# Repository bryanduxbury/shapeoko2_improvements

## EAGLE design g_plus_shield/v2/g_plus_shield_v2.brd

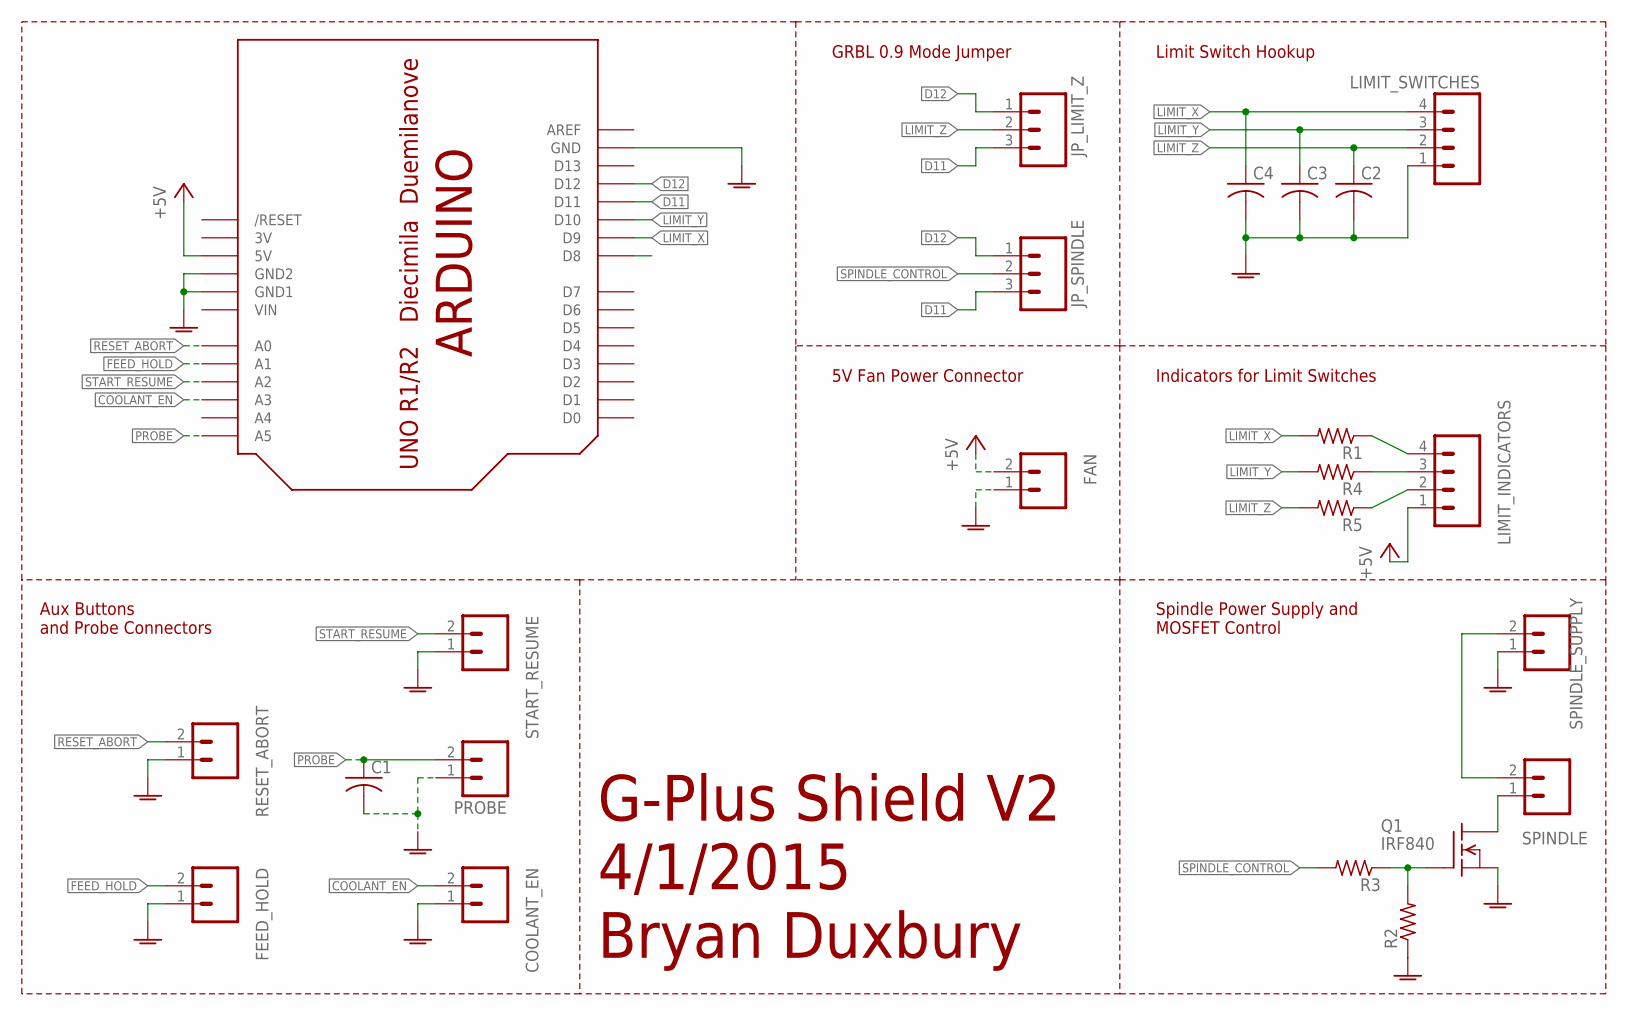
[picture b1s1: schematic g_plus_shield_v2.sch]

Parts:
C1, C2, C3, C4: C-US050-024X044; C050-024X044
COOLANT_EN: M02POLAR; MOLEX-1X2
FAN: M02POLAR; MOLEX-1X2
FEED_HOLD: M02POLAR; MOLEX-1X2
JP_LIMIT_Z: M03POLAR; MOLEX-1X3
JP_SPINDLE: M03POLAR; MOLEX-1X3
LIMIT_INDICATORS: M04POLAR; MOLEX-1X4
LIMIT_SWITCHES: M04POLAR; MOLEX-1X4
PROBE: M02POLAR; MOLEX-1X2
Q1: IRF840; TO220
R1, R2, R3, R4, R5: R-US_0207/7; 0207/7
RESET_ABORT: M02POLAR; MOLEX-1X2
SPINDLE: M02POLAR; MOLEX-1X2
SPINDLE_SUPPLY: M02POLAR; MOLEX-1X2
START_RESUME: M02POLAR; MOLEX-1X2
U$1: ARDUINO-NODIM

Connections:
3V: U$1.3V
48V: SPINDLE.2, SPINDLE_SUPPLY.2
+5V: FAN.2, LIMIT_INDICATORS.1, U$1.5V
COOLANT_EN: COOLANT_EN.2, U$1.A3
D11: JP_LIMIT_Z.3, JP_SPINDLE.3, U$1.D11
D12: JP_LIMIT_Z.1, JP_SPINDLE.1, U$1.D12
FEED_HOLD: FEED_HOLD.2, U$1.A1
GNDA: C1.2, C2.2, C3.2, C4.2, COOLANT_EN.1, FAN.1, FEED_HOLD.1, LIMIT_SWITCHES.1, PROBE.1, Q1.3 (S), R2.1, RESET_ABORT.1, SPINDLE_SUPPLY.1, START_RESUME.1, U$1.GND, U$1.GND1, U$1.GND2
LIMIT_X: C4.1, LIMIT_SWITCHES.4, R1.2, U$1.D9
LIMIT_Y: C3.1, LIMIT_SWITCHES.3, R4.2, U$1.D10
LIMIT_Z: C2.1, JP_LIMIT_Z.2, LIMIT_SWITCHES.2, R5.2
unnamed: LIMIT_INDICATORS.4, R1.1
unnamed: Q1.2 (D), SPINDLE.1
unnamed: Q1.1 (G), R2.2, R3.1
unnamed: LIMIT_INDICATORS.2, R5.1
unnamed: LIMIT_INDICATORS.3, R4.1
PROBE: C1.1, PROBE.2, U$1.A5
RESET_ABORT: RESET_ABORT.2, U$1.A0
SPINDLE_CONTROL: JP_SPINDLE.2, R3.2
START_RESUME: START_RESUME.2, U$1.A2
VIN: U$1.VIN

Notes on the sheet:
GRBL 0.9 Mode Jumper
Limit Switch Hookup
Indicators for Limit Switches
Spindle Power Supply and MOSFET Control
Aux Buttons and Probe Connectors
5V Fan Power Connector
G-Plus Shield V2 4/1/2015 Bryan Duxbury

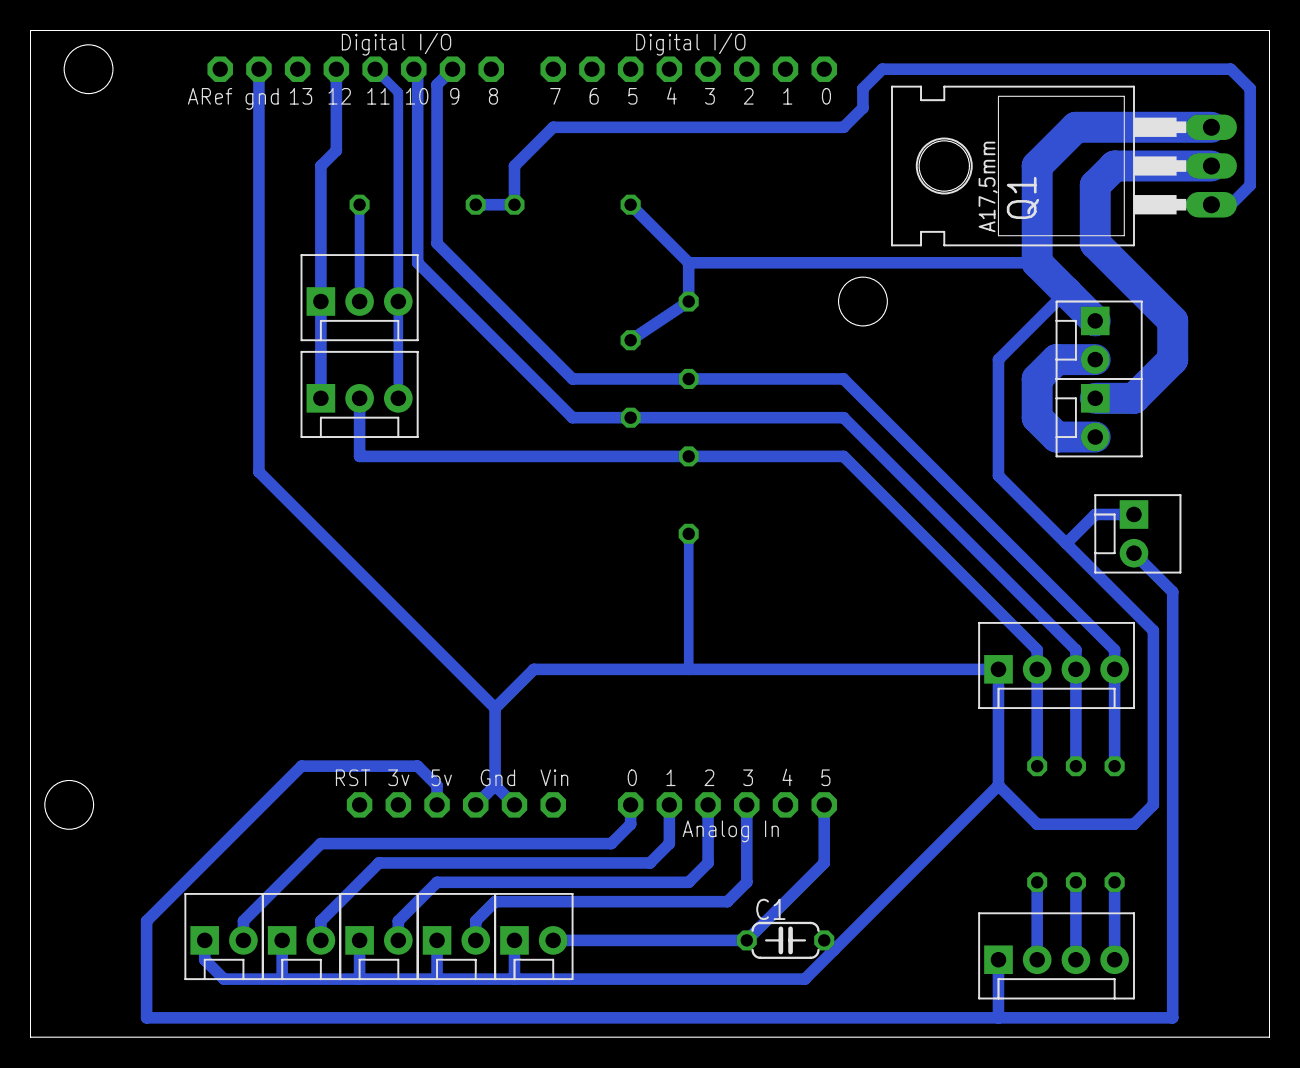
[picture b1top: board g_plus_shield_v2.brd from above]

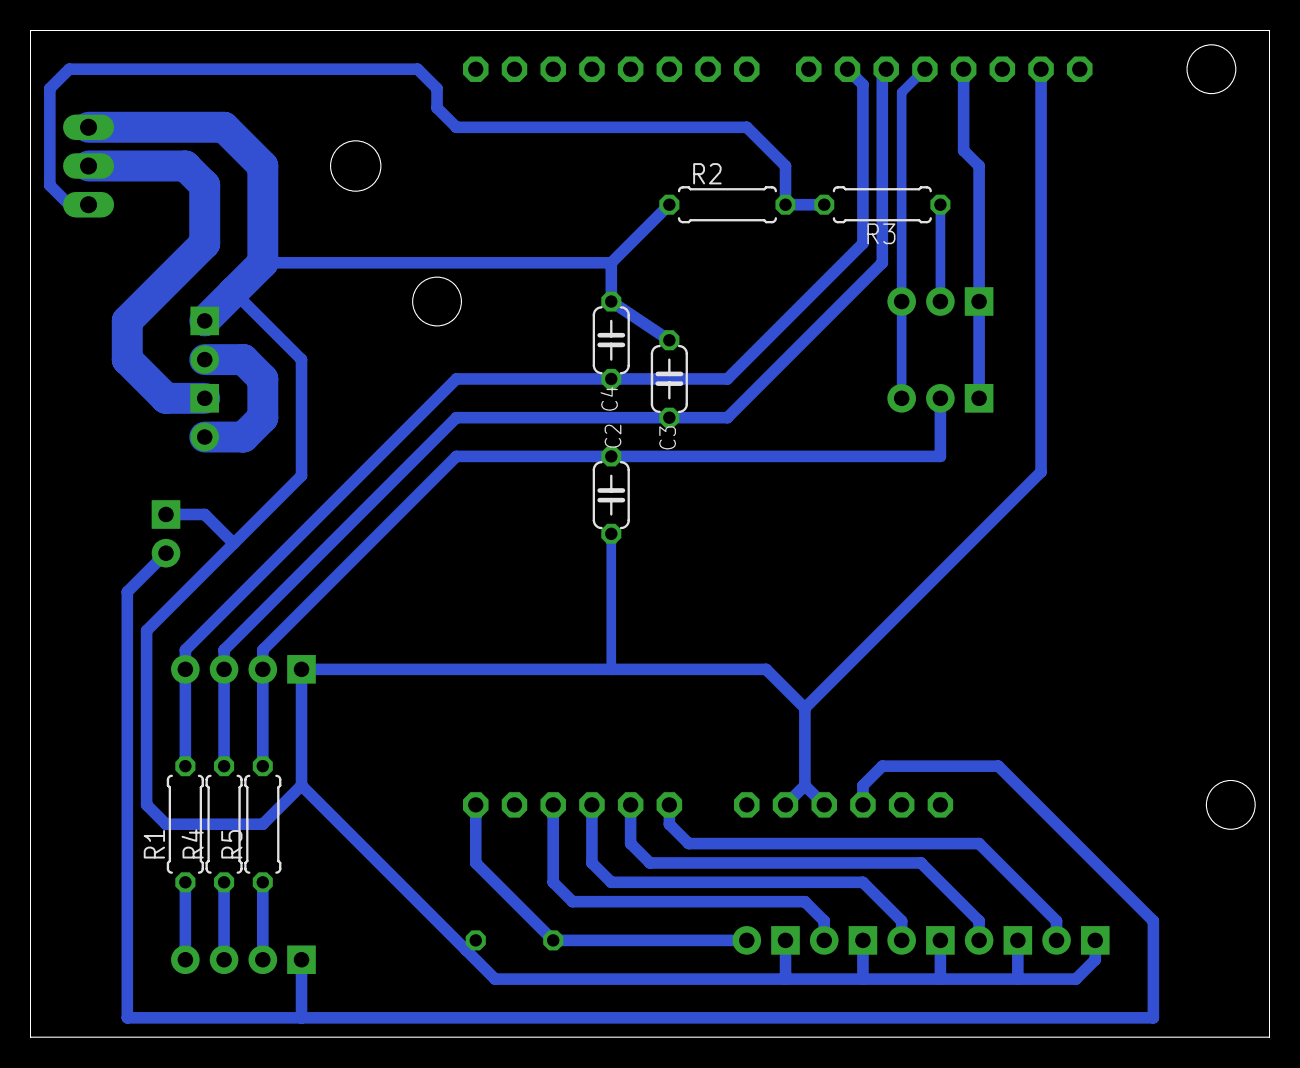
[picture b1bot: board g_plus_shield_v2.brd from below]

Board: 2 copper layers, 81.3 x 66.0 mm, 23 parts (8 on the bottom side), 19 nets.

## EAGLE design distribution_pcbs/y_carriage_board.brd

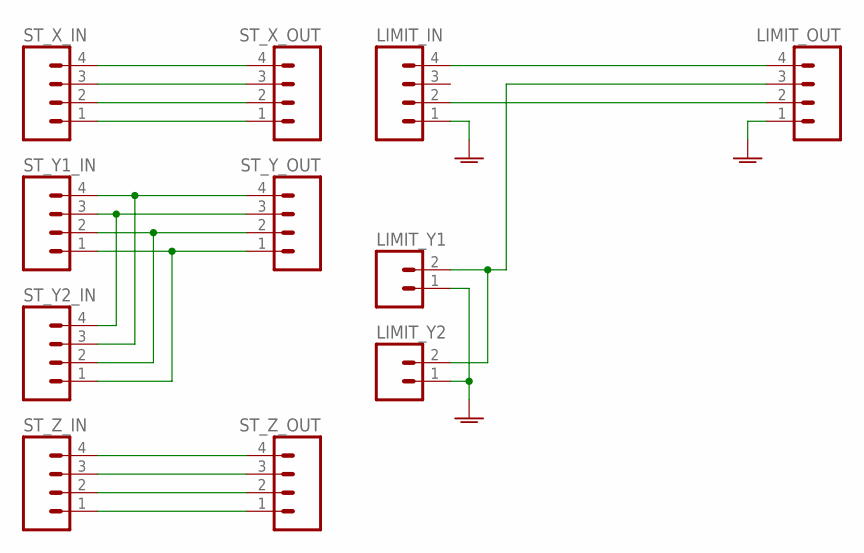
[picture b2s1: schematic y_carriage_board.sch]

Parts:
LIMIT_IN: M04POLAR; MOLEX-1X4
LIMIT_OUT: M04POLAR; MOLEX-1X4
LIMIT_Y1, LIMIT_Y2: M02POLAR; MOLEX-1X2
ST_X_IN: M04POLAR; MOLEX-1X4
ST_X_OUT: M04POLAR; MOLEX-1X4
ST_Y1_IN, ST_Y2_IN: M04POLAR; MOLEX-1X4
ST_Y_OUT: M04POLAR; MOLEX-1X4
ST_Z_IN: M04POLAR; MOLEX-1X4
ST_Z_OUT: M04POLAR; MOLEX-1X4

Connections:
GNDA: LIMIT_IN.1, LIMIT_OUT.1, LIMIT_Y1.1, LIMIT_Y2.1
unnamed: ST_X_IN.4, ST_X_OUT.4
unnamed: ST_X_IN.3, ST_X_OUT.3
unnamed: ST_X_IN.2, ST_X_OUT.2
unnamed: ST_X_IN.1, ST_X_OUT.1
unnamed: ST_Y1_IN.2, ST_Y2_IN.2, ST_Y_OUT.2
unnamed: ST_Y1_IN.1, ST_Y2_IN.1, ST_Y_OUT.1
unnamed: LIMIT_IN.4, LIMIT_OUT.4
unnamed: LIMIT_OUT.3, LIMIT_Y1.2, LIMIT_Y2.2
unnamed: ST_Z_IN.4, ST_Z_OUT.4
unnamed: ST_Z_IN.3, ST_Z_OUT.3
unnamed: ST_Z_IN.2, ST_Z_OUT.2
unnamed: ST_Z_IN.1, ST_Z_OUT.1
unnamed: LIMIT_IN.2, LIMIT_OUT.2
unnamed: ST_Y1_IN.3, ST_Y2_IN.4, ST_Y_OUT.3
unnamed: ST_Y1_IN.4, ST_Y2_IN.3, ST_Y_OUT.4

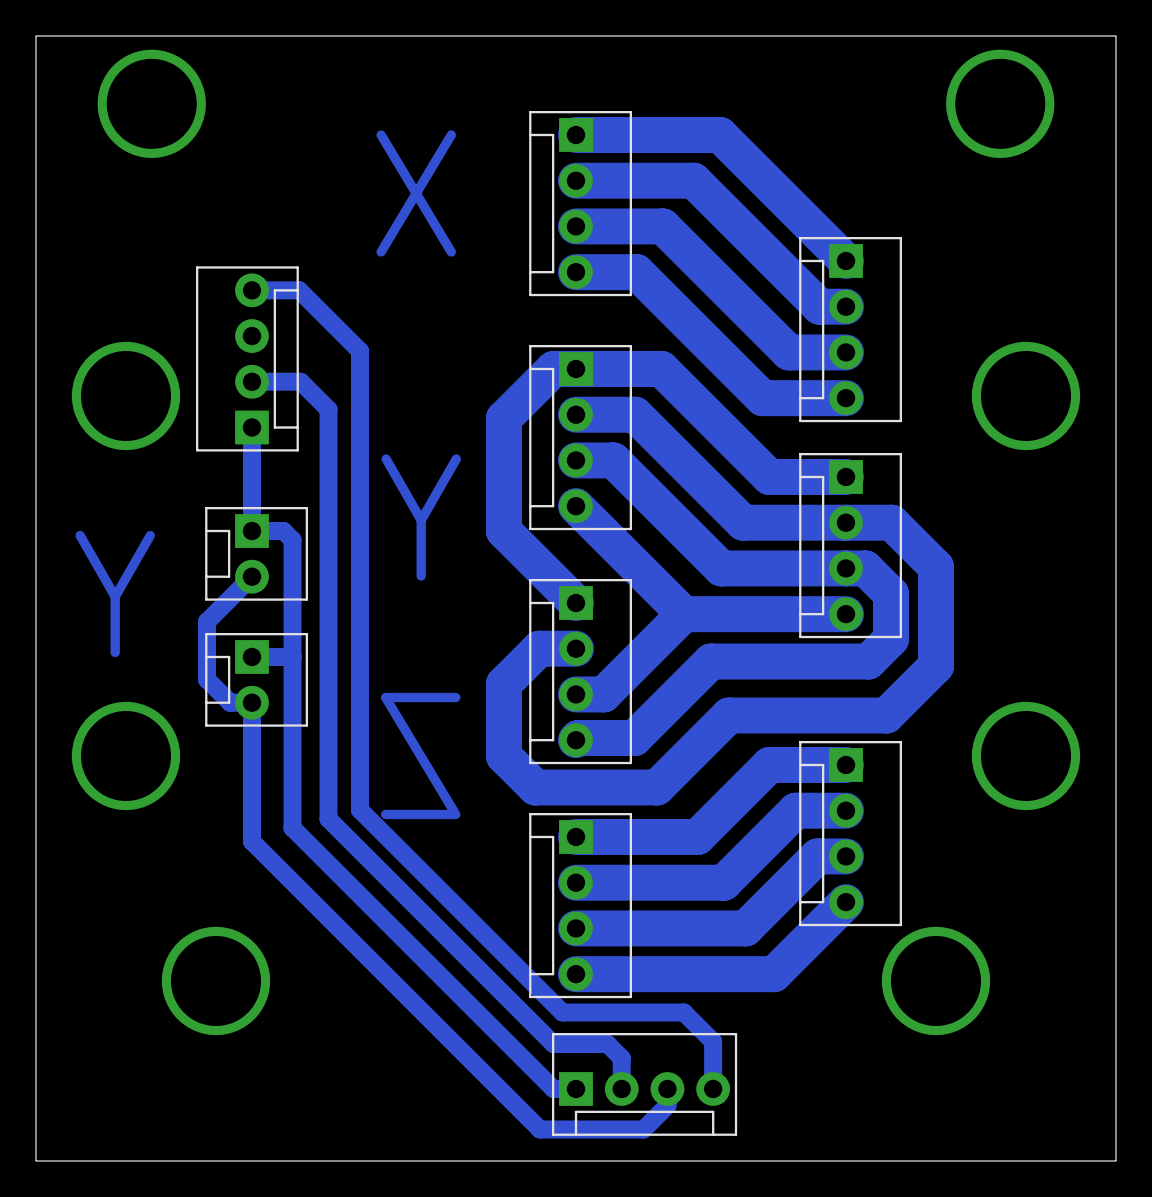
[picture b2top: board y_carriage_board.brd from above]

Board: 2 copper layers, 60.0 x 62.5 mm, 11 parts (0 on the bottom side), 16 nets.

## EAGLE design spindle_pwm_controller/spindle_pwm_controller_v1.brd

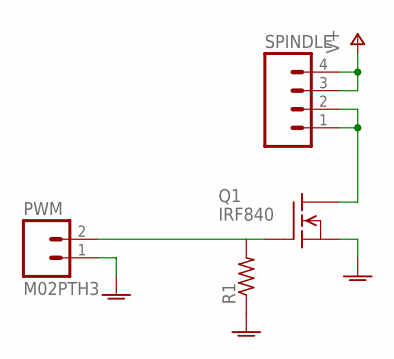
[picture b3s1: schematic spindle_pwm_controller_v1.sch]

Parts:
PWM: M02PTH3; 1X02_LONGPADS
Q1: IRF840; TO220
R1: R-US_0207/7; 0207/7
SPINDLE: M04LONGPADS; 1X04_LONGPADS

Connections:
GNDA: PWM.1, Q1.3 (S), R1.1
unnamed: Q1.2 (D), SPINDLE.1, SPINDLE.2
unnamed: PWM.2, Q1.1 (G), R1.2
V+: SPINDLE.3, SPINDLE.4

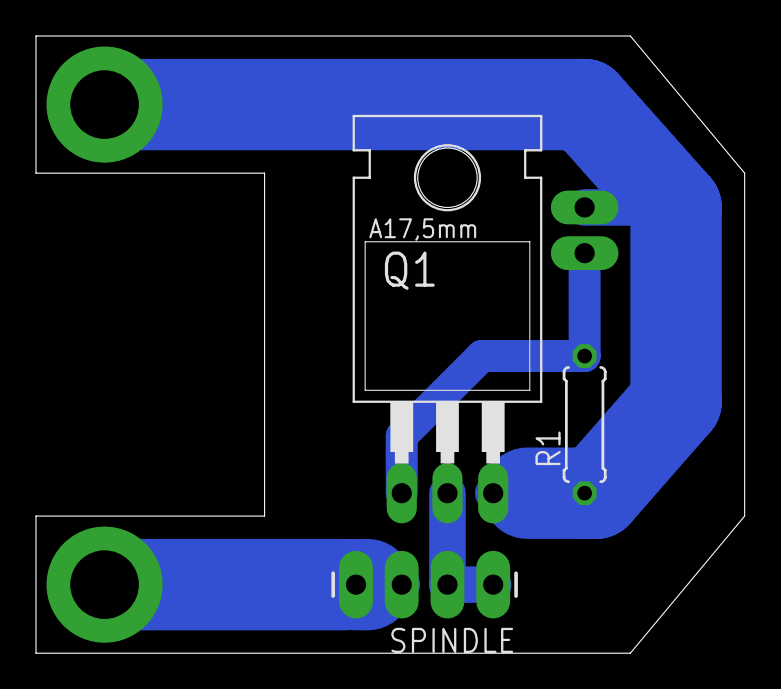
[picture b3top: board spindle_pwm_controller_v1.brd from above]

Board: 2 copper layers, 39.4 x 34.3 mm, 4 parts (0 on the bottom side), 4 nets.

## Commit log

2014-11-16 init commit of controls enclosure
2014-11-16 swag at an endplate adapter for arduino
2014-11-16 two very simple designs for screw-down clamps, intended to go with a wasteboard using threaded inserts
2014-11-16 scadfile to help generate an array of holes and counterbores for installing threaded inserts in wasteboard
2014-11-16 add gitignore to filter out gcode files
2014-11-19 design for makerslide-mounted limit switch adapter
2014-11-19 added clamp version designed to accommodate threaded insert
2014-11-19 change tabbing scheme on controls enclosure
2014-11-21 so many improvements
2014-11-25 gitignore for eagle temp files
2014-11-25 first draft of pcbs for stepper and limit connectors on carriages
2014-11-25 jig for holding 100x100 pcb blanks for isolation milling
2014-11-27 add script to add feed speed when there isn't any specified
2014-11-27 draft of adapter plate for z-limit swtich
2014-11-27 shrink one of the traces to meet clearance requirements
2014-11-27 update gitignore for more eagle temp files
2014-12-04 version of z limit switch plate that finally works
2014-12-04 simple calibration pattern used to solve for steps/mm
2014-12-04 shrink milling jig vertically, add counterbores to insert holes
2014-12-08 added external connectors board model plus cutouts
2014-12-08 change widths and board dimensions
2014-12-08 some hacks to make the part cuttable in multiple passes
2014-12-08 script to post-process gcode to set safe z higher than eagle wants to generate
2014-12-08 adjust board height and trace width
2014-12-09 change trace widths on y carriage board
2014-12-15 -factor individual models out of various designs; make the endplate arduino mount into a proper control panel etc
2015-01-06 concept for an aluminum extrusion cnc cart
2015-01-06 extrusion outline
2015-01-06 gusseted bracket model
2015-03-29 lots and lots of changes
2015-04-02 g-plus shield schematic and layout
2015-08-13 outstanding work

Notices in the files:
parts and their libraries:
SparkFun-Connectors: Licensing: Creative Commons ShareAlike 4.0 International - https://creativecommons.org/licenses/by-sa/4.0
